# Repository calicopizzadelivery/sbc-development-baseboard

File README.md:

# sbc-development-baseboard

One board carrying the hardware you need to develop on and remotely manage an
attached single-board computer: a microcontroller that is a USB device to the
target and a console to you, four individually switched USB-A ports, an FTDI
header straight to the workstation, two isolated
SPDT relays on screw terminals, a level-shifted serial console, and a switched
supply for the target itself.

It replaces a bench that currently takes an FRDM-K64F, a QT Py, an 8-channel
relay board, a two-tier USB hub cascade and a CP2102N dongle, wired together by
hand and documented in a port map that has to be re-surveyed whenever anything
is replugged.

## What it does

| Function | How |
|---|---|
| Type at the target | USB HID keyboard + mouse from the K64's device port |
| Cut power to any USB device | Four USB-A ports on two stacked receptacles, each with its own current-limited switch |
| Hard power-cycle the target | Switched +5V_TGT rail up to 3 A behind an eFuse, or any PSU up to 30 V / 5 A through an isolated relay |
| Toggle target I/O — FORCE_RECOVERY and friends | Two SPDT relays, dry contacts, Phoenix terminals |
| Read the target's serial console | MCU-owned UART, auto level translation 1.2–3.6 V |
| Read it from the workstation directly | FT231X on an internal hub port, standard 6-pin FTDI header, 3.3 V |
| Do all of it from somewhere else | 10/100 Ethernet to the workstation |
| Do all of it with no network | USB CDC console over the onboard DAPLink |

Every one of those is addressable from the same ASCII protocol the relay
controller and the HID injector already speak — one line in, one line out,
starting `OK` or `ERR`. See **[docs/protocol.md](docs/protocol.md)**.

## The shape of it

```
workstation ──USB-C──> hub ──> 4x USB-A (switched)     ──> whatever you hang on the bench
                           ──> FT231X, FTDI header     ──> target's console, direct
            ──RJ45───> K64 ──> USB-C device port       ──> target's USB host port
                           ──> UART + VREF             ──> target's console
                           ──> 2x SPDT dry contacts    ──> target's recovery/reset pins
                           ──> switched +5V, 3 A       ──> target's supply
 target PSU ──Phoenix──> isolated relay, NO, 5 A       ──> target's supply, any voltage
 5 V adapter ──barrel──> +5V, one rail, 4 A, 20 W      ──> everything but the passthrough
```

140 × 100 mm, four M3 corner holes. Your connectors leave the left edge, the
target's the right; an LED on every rail, every switched output and every relay
coil, and none on the passthrough, whose voltage is whatever you plugged in.

One USB-C for the workstation and a barrel jack for power (2026-10-10; two
USB-C inlets, a PD charger beside the workstation port, until then). A
workstation port that carries data offers 15 W at best, and four switched ports
plus a target rail need more than that, so power has its own connector: a
5 V 4 A adapter on a 2.5 mm barrel jack, 20 W, which firmware budgets across
the ports and the target rail. A USB-C PD sink feeding two 5 V bucks did that
job first, and went because of what it cost the board rather than the bench:
339 parts became 270, and the one rail layer no longer carries a 3 A inlet
beside two 6 A rails, which is where the router stalled at 98 open connections
on six layers. Keeping power off the workstation link also means the board stays
alive when that link is down, so the MCU can power-cycle the entire USB tree
including its own path back to you.

## Where the design came from

Most of the non-obvious decisions here are bench scars from the Jetson work, not
preferences. They are written up in full in
**[docs/hardware-spec.md](docs/hardware-spec.md)**; the short version:

- **Nothing the MCU depends on sits downstream of a switch it controls.** The
  DAPLink, the Ethernet PHY and the MCU itself are all upstream. `OFF ALL` can
  never take out the console.
- **Rails boot to the state that does no harm.** USB ports and the target rail
  come up powered; relays come up de-energized. Resistors set this while the MCU
  is still in reset, so a reset never drops a load or asserts recovery.
- **The device port cannot back-feed the target.** Its VBUS is sense-only
  through a blocking element. This is the fix for the failure where cutting the
  target's power left it half-alive for 90 seconds because a self-powered
  FRDM-K64F was pushing 5 V up its own device port.
- **The relays are signal relays with gold-clad contacts.** Switching a 1.8 V
  logic pin is a dry circuit; silver power-relay contacts grow an oxide film
  that such a signal cannot break down.
- **The MCU owns the target's console.** No USB-UART bridge to wedge and look
  exactly like a target that is not booting.
- **The target's PSU passes through on its own nets.** A 19 V / 3 A return
  current has no business on the board's ground plane or its USB shields. It
  crosses one relay contact — normally open — so nothing powers until the
  baseboard says so, and a dead baseboard leaves the target off.

## Status

Specification, a generated schematic (KiCad 10, a root sheet and eight sub-sheets, ERC clean) and
a generated, placed six-layer board, both in
[`hardware/kicad/sbc-baseboard/`](hardware/kicad/sbc-baseboard/) with a
[PDF](hardware/kicad/sbc-baseboard/sbc-baseboard.pdf) of the schematic for
review. The board is placed and bulk-routed by the house standard's engine
(see [hardware/kicad/README.md](hardware/kicad/README.md)) and is being
routed again for the barrel-jack inlet (2026-10-10; the board routed before
it, with the PD inlet and the two bucks, stopped at 98 open connections on
six layers and 116 on four); the hand pass that finishes the routing is open.
No firmware.

Next: the routing and the hand pass on the board, then firmware.

## Layout

```
docs/hardware-spec.md   block diagram, part selection, power and pin budgets,
                        safe states, and the open questions
docs/protocol.md        the console protocol, across both transports
docs/block-diagram.*    the diagram above, SVG source and rendered PNG
scripts/block-diagram.py regenerates both; run it with every configuration change
hardware/kicad/         the KiCad project (sbc-baseboard/) and the generator that
                        produced its first pass (gen/) — see hardware/kicad/README.md
hardware/datasheets/    the parts that matter
```

## Related

- [`frdm-k64f-hid`](../frdm-k64f-hid) — the HID injector firmware this board inherits
- [`qtpy-relay-controller`](../qtpy-relay-controller) — the relay protocol and its safe-state rules
- [`nvidia-jetson-tv`](../nvidia-jetson-tv) — the target that motivated all of it

## Licence

Apache-2.0. See [LICENSE](LICENSE).

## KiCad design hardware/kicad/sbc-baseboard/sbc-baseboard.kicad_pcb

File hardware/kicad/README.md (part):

# KiCad project

`sbc-baseboard/` is the KiCad 10 project: a root sheet and eight sub-sheets,
a project symbol library for the parts the standard libraries lack, an ERC
report, a PDF of every sheet and a BOM.

```
sbc-baseboard/
  sbc-baseboard.kicad_pro   project
  sbc-baseboard.kicad_sch   root: sheet index, mounting holes, the verify-before-fab list
  power.kicad_sch           barrel-jack inlet J2, its TVS and reverse-polarity FET, +5V bulk, the +3V3 buck
  mcu.kicad_sch             K64, USB device port J3, SWD J16, heartbeat
  ethernet.kicad_sch        KSZ8081RNA, magjack
  hub.kicad_sch             USB2517, upstream J1, four switched USB-A, FT231X switch
  ftdi.kicad_sch            FT231X, J9 header, jumpers
  daplink.kicad_sch         MK20DX128 DAPLink
  target.kicad_sch          console, GPIO/I2C breakout, +5V_TGT eFuse
  relays.kicad_sch          two signal relays, PSU passthrough relay and its opto monitor
  libs/                     the house symbol libraries (ecad-libraries), a git submodule pinned to a tag
  sym-lib-table             names them calico-ic and calico-electromechanical, as ${KIPRJMOD}/../libs/...
                            and the stacked USB-A as two units (one per port)
  sbc-baseboard.pdf         all nine sheets
  erc.txt, bom.csv
```

Reference designators are numbered by sheet: R1xx/C1xx power (the inlet
and the +3V3 buck), 2xx MCU, 3xx Ethernet, 4xx hub, 5xx FTDI, 6xx DAPLink,
7xx target I/O (the +5V_TGT eFuse among them), 8xx relays and passthrough.

## How it was made, and the handoff

The schematic was **generated**, by `gen/build.py`. That generator pulls
symbols from KiCad's own libraries (so the embedded copies match what KiCad
ships), builds the missing symbols from datasheet pin tables, lays each sheet
out around its main component (`gen/fanout.py`: lanes leave the IC's pins at
pin pitch, and connectors, series parts, pull-ups and power symbols are drawn
at the ends of the lanes — the style in
[ecad-standards](https://github.com/calicopizzadelivery/ecad-standards)), and
writes the `.kicad_sch` files directly. It then runs `kicad-cli sch erc` and
exports the PDF and BOM. Pin-position maths and power-symbol net naming were
calibrated against `kicad-cli`'s netlist export before any real sheet was
built.

Five checks guard every build and all pass at zero: `kicad-cli sch erc
--severity-all`; `gen/check_geom.py`, which finds wire ends and pin ends that
land on a foreign wire with no junction (the shorts a netlist shows only as a
merged net) and any two wires drawn over each other;
`gen/netcheck.py`, which traces wire-level connectivity in each sheet and
reports any net carrying two rails; and `gen/check_layout.py`, which reports
text over outlines, wires or other text, wires through a part body, and power
symbols pointing the wrong way (GND always hangs down, rails always stand up),
anything on the sheet frame or the title block, pin numbers treated as text
like any other, and pin names inside a symbol that print over each other
(`gen/check_pins.py`, run on library symbols too; its `--gaps` option lists the
closest name pairs). Text widths come from a per-glyph table fitted to the text
extents KiCad writes into its own PDF export. The fifth is reproducibility:
build, `git add` the outputs, build again, and `git status` must be empty. The netlist was also diffed against the
first label-style pass with passive renumbering factored out, so the re-layout
changed drawing, not connectivity (the JP501 default and the J1 VBUS divider
tap, which became a local label, are the two intended exceptions).

**Nothing is drawn over anything else.** Routes into a stacked connector
from one side take staggered columns and rows (the route bound for the
farthest pin gets the outermost column and the nearest row), a tag before a
route ends where the route's target lies, several routes into one pin share
one stub, and a second tap on a wire lands beside the first, never on it.
The geometry check is at zero on every sheet: no wire end on a foreign wire
without a junction, no two wires sharing a stretch.

**The FTDI header is an Adafruit FTDI Friend.** J9 is GND, CTS, VCC, TX, RX,
RTS in that order; VCC is 5 V by default (JP502, bridged A–C) or 3.3 V from
the FT231X's regulator (B–C); pin 6 is RTS by default (JP501, bridged A–C)
or DTR. Logic is 3.3 V. The first pass left J9's VCC pin on an open jumper
only, so it floated by default; the bridged jumpers fix that.

**The DAPLink K20 follows the FRDM-K64F OpenSDA circuit.** DAPLink's k20dx
port reads SWDIO on PTC7 and drives it on PTC6, so both are on the SWDIO
net; the FRDM's 33 Ω series resistors on the K20's USB pair are fitted. See
[reference-design-review.md](../../docs/reference-design-review.md).

**Differential pairs are named for the router.** Every USB 2.0 pair carries
net names `<base>_P` / `<base>_N`, the suffixes KiCad's PCB editor pairs up:
`J1_D`, `J3_D` and `PORT1_D`..`PORT4_D` on the receptacle side of each ESD
array, `HUB_UP` and `HUB_DN1`..`HUB_DN7` at the hub, `K64_USB` and
`FTDI_USB` at the chips (the ESD arrays' pass-through pins and the FT231X's
series resistors each split a pair into two nets, and both halves are named).
The project file carries a `USB` net class matched by pattern
(`*_USB_?`, `*_D_?`, `*HUB_UP_?`, `*HUB_DN?_?`); the patterns are globs over
the full hierarchical name, so a sheet-local net such as `/USB hub/PORT1_VBUS`
is matched only by a pattern that starts with `*` (the port VBUS nets sat in
`Default` until 2026-10-08 for want of that star, and the standard's engine
now stops on a class that no net resolves to). Its differential width and
gap are 0.33 / 0.20 mm, 90 Ω over the ground plane beside each outer layer on
the six-layer stackup (the fab's calculator rules when the stackup is
confirmed); the `ETH` class 0.29 / 0.25 mm for 100 Ω. Route each pair as a pair, no stubs,
over an unbroken reference plane. The power classes are matched the same
way: `PWR_4A` (2.5 mm tracks or pours, 1.0 mm / 0.5 mm vias, three rail vias
per pad) for `+5V` and `*+5V_TGT`, the one inlet rail and the eFuse's
switched output (2026-10-10; until then `PWR_6A` carried the two bucks'
6 A outputs and the PD inlet's `VBUS_IN` ran at 3 A); `USB_VBUS_3A` (2 mm,
1.0 mm vias) for `*PORT?_VBUS` and `*FTDI_VBUS` only; `PWR_1A` (0.6 mm) for
`+3V3`; `PSU_3A` and `PSU_ISO` for the passthrough and its sense lines;
`Default` at 0.2 mm.

**Builds are reproducible.** Every UUID in the generated files is derived,
not drawn: a UUID5 in a namespace made from the project name, keyed by what
the element is (a symbol by its reference and unit, a pin by its symbol, a
wire by its sheet and ends, a label by its sheet, net and position, a sheet by
its file name; identical keys get a counter in draw order). The ERC report
header and the PDF's creation date are pinned to the title-block date. So two
builds of one design give byte-identical files, a commit touches only the
sheets whose design changed, and once layout starts a regenerated sheet keeps
its footprints linked, since the board links footprints to symbols by UUID
path. The costs are the ones KiCad itself has: renaming a reference is a new
symbol, moving a wire or label is a new UUID (nothing outside the sheet refers
to those), and the power symbols, numbered in draw order per sheet, renumber
when one is inserted before them. Keep it that way: never write a random UUID
into the output, and never let an export's timestamp into a tracked file.

**The generator is bring-up tooling, not the source of truth.** The moment
anyone edits the schematic in KiCad, the KiCad files are the design and
`gen/` is history: re-running `build.py` would overwrite the edits. The honest
next step is layout.

```bash
cd gen && ./build.py        # regenerate everything (only while nothing has been hand-edited)
```

## Layout

The board file `sbc-baseboard.kicad_pcb` was generated once, by the
standard's placement engine (`standards/tools/placer.py`, the ecad-standards
repository as a submodule at `standards/`, on KiCad's `pcbnew` Python module)
called from `gen/pcb.py`, from the schematic's netlist, the project file and
the directives in `gen/layout.py`, which are
[docs/layout-directives.md](../../docs/layout-directives.md) as data. It
carries the 140 × 100 mm outline with 2 mm corners, the four M3 holes on GND
7 mm from the corners with their corner keep-outs, Advanced Circuits' 6-layer
stackup, the 270 footprints with their nets (339 until 2026-10-10, when the
USB-C PD inlet, its STUSB4500 controller, bus buffer and programming header
and the two 5 V bucks went and a barrel jack came; 481 connections, 499
before), the L2 and L5 ground planes with the isolated PSU_GND islands, and
`sbc-baseboard.kicad_dru` with the passthrough's isolation rules.

The placement follows
[ecad-standards/layout.md](https://github.com/calicopizzadelivery/ecad-standards/blob/main/layout.md)
section 3: the edge connectors are locked at the directives' positions,
facing outward; the ICs are anchored by flow (the table in the directives:
power enters at J2 on the left edge, its reverse-polarity FET Q101 anchored
at (20, 30) behind the jack with the TVS, gate pull-down, bulk capacitors
and LED around it as the inlet island, the +3V3 buck U105 at (41, 41) as
the one regulator city, laid out from its datasheet figure, and the eFuse
U704 behind J14; the corner the two bucks occupied, x 10..70, y 3..36, is
largely empty since 2026-10-10);
the two parts that straddle the isolation barrier are fixed; every other
part is placed at the pin it serves, by the generator, in five passes (small
decoupling capacitors at their pins, the large parts on an IC's own pins,
bulk capacitors, the small parts on those pins, then parts hosted by other
passives), each on its host's nearest side with the pad on the host's net
facing it, packed outward in rings; since 2026-10-10 the owner's hand
placement outranks all of this (the directives' Placement section: the
saved board is harvested into `gen/hand_placement.py` by the standard's
`tools/handplace.py`, every part fixed where the owner put it, and the
generator reproduces it), so the engine's own placement is what a part
gets until the owner moves it; since 2026-10-15 the standard's `tools/live.py`
runs the lane check on the board open in the PCB editor over KiCad's IPC
API and selects the parts that stand in a lane, so a move is judged as it
is made (from this directory: `standards/tools/bootstrap.sh` once, "Enable
KiCad API" in KiCad's preferences, then `standards/.venv/bin/python
standards/tools/live.py check gen --select`). Small resistors, capacitors, diodes and
transistors that are not on a current-carrying, pair or switching-loop net go
to the bottom, tucked under their host's pin row, clear of through-hole pads
and exposed-pad via fields (the directives' Sides section); the rest stay on
top. The lanes the directives declare (the PSU passthrough: J18 to the relay
to J19) are laid first as footprint keep-outs on both sides and as 2 mm
tracks, so nothing is placed in the way of the 3 A path. ESD parts go down
before anything else, on top, in the first ring at their connector's signal
pins; the USB arrays are flow-through, turned with their receptacle-side
pins toward the receptacle, and both nets of each pair are in the `USB`
class (the schematic build refuses a `_P`/`_N` pair outside it). `placement.txt`
records every part's host, side and ring; the generator prints the parts it
could not keep within 8 mm of their pin. The silkscreen pass places each reference designator where it
overlaps nothing (1.0 mm, then 0.8 mm text) and omits it otherwise, per the
standard's section 6; ICs and connectors are never omitted, their designator
steps out to the nearest pocket instead, and the generator lists those too.
The fabrication layer keeps every designator.

The pairs are laid by the engine as pair lanes (both members at the class's
differential geometry, escapes, the USB-C bridges, two layer changes where
a pair must pass under the port pairs, lengths matched by a bump), the ESD
arrays and series parts anchored for it; the PSU passthrough is laid as
single-net lanes; the one rail, +5V, is a chain of rectangles on L4
referenced to the L5 ground plane, from the jack (x 3..42, y 22..40)
through the 3V3 buck's input, down beside the relay region, along the port
switches, across above the passthrough region to the FTDI switch, the
relays and the eFuse behind J14, which the standard's rails gate holds to
one piece (2026-10-10; until then VBUS_IN, +5V_PORTS and +5V_TGT were
three rails on that layer, the two 6 A ones and the 3 A inlet competing
for it); +5V_TGT leaves the eFuse to J14 as a track in the same class;
+3V3 is routed, in its 0.6 mm `PWR_1A` class, since on six layers a plane
for it would cost the third routing layer. What is left is routed by
FreeRouting through the standard's `tools/autoroute.py` with all of that
locked (`gen/pcb.py --route`; the directives' `FREEROUTING` setting names
the binary), and the hand pass finishes from there. KiCad Routing Tools
was tried on the same board as a second opinion (2026-10-07): two hours in
it had 25 connections left and 1 646 DRC errors, having routed below the
fab's track and via floors and through the keep-outs; FreeRouting honours
the Specctra rules and the fixed lanes, so it stays the bulk router.

`gen/pcb.py` also runs `kicad-cli pcb drc --severity-all --refill-zones`
(the planes are filled for the check and not saved, so a plane that fails to
fill or strays into a keep-out shows; the unconnected count is the ratsnest's
and does not credit the planes); its report is `drc.txt`.

The board as last routed (2026-10-09, six layers, with the PD inlet and the
two bucks still on it; the barrel-jack board of 2026-10-10 started from a
copper reset and is being placed by hand before it is routed again, so
until that routing is committed these are the previous board's figures) is the engine's
placement on the 140 × 100 mm outline, bulk-routed by FreeRouting on L1,
L3 and L6 over the locked lanes, rail vias and planes (`gen/pcb.py --route
--copper`, 24 passes, 5 h 12 min on one thread of which 55 min were its
fanout stage, 122 open connections by its own count after its optimiser)
and given the standard's copper pass: 3 050 track segments, 42 % of the
track length on the top, 37 % on L3 and 21 % on the bottom (of the
router's own, 47 % on L3); 939 vias, of which 237 are the rail vias beside
the pads on the plane nets (156 on ground, 39 on +5V_PORTS, 26 on VBUS_IN,
14 on +5V_TGT, 2 on the passthrough's ground; 14 pads fewer than their
class's count and 115 none at all, both listed in `placement.txt`), 24 the
lanes' own layer changes, 332 ground stitching on the 5 mm grid (2.3
stitching vias per cm² outside the isolated region, 3.5 ground vias per
cm² with the rail vias) and 346 the router's; ground floods over 54 % of
the top and 67 % of the bottom, notched around the passthrough block,
which floods its own `PSU_GND`, all saved filled; the ground planes on L2
and L5 over 76 % each. The three L4 rails are each one piece; +3V3 is
routed at 0.6 mm, 243 segments and 496 mm. The 282 lane tracks are locked
and intact: nine pairs matched to 0.00 mm (six by bumps, three by
symmetric legs), the two Ethernet pairs 2.5 mm apart over their 7.4 to
10.9 mm from jack to PHY, where no bump fits. The router laid the wide
classes at the 2 mm cap apart from the pad-entry necks; five segments run
on at a pad's width more than a millimetre beyond the pad (three on +3V3,
one each on +5V_PORTS and FTDI_VBUS) and are listed for the hand pass to
widen. 98 of the 499 connections
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
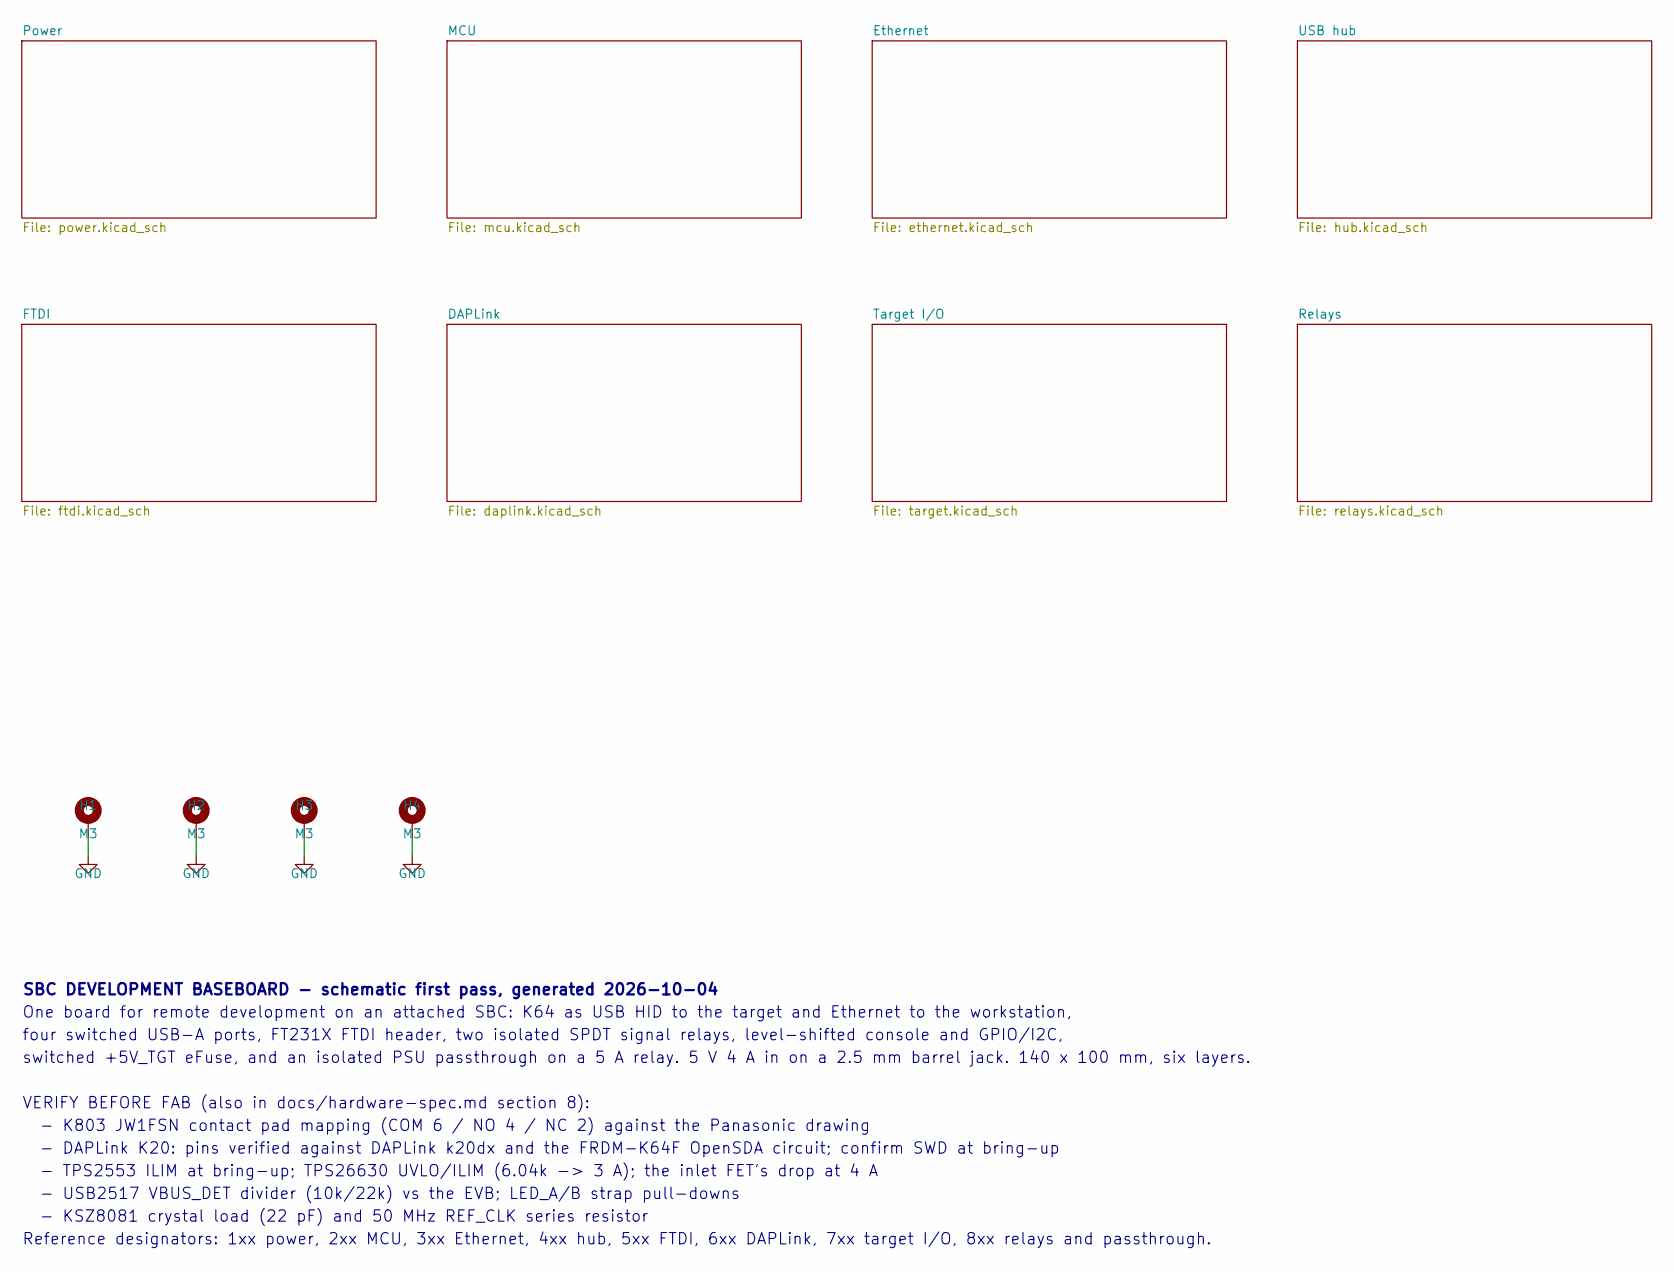
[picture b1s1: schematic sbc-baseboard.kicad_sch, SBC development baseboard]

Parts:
H1, H2, H3, H4: M3; MountingHole_3.2mm_M3_Pad

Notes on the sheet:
SBC DEVELOPMENT BASEBOARD - schematic first pass, generated 2026-10-04
One board for remote development on an attached SBC: K64 as USB HID to the target and Ethernet to the workstation,
four switched USB-A ports, FT231X FTDI header, two isolated SPDT signal relays, level-shifted console and GPIO/I2C,
switched +5V_TGT eFuse, and an isolated PSU passthrough on a 5 A relay. 5 V 4 A in on a 2.5 mm barrel jack. 140 x 100 mm, six layers.
VERIFY BEFORE FAB (also in docs/hardware-spec.md section 8):
- K803 JW1FSN contact pad mapping (COM 6 / NO 4 / NC 2) against the Panasonic drawing
- DAPLink K20: pins verified against DAPLink k20dx and the FRDM-K64F OpenSDA circuit; confirm SWD at bring-up
- TPS2553 ILIM at bring-up; TPS26630 UVLO/ILIM (6.04k -> 3 A); the inlet FET's drop at 4 A
- USB2517 VBUS_DET divider (10k/22k) vs the EVB; LED_A/B strap pull-downs
- KSZ8081 crystal load (22 pF) and 50 MHz REF_CLK series resistor
Reference designators: 1xx power, 2xx MCU, 3xx Ethernet, 4xx hub, 5xx FTDI, 6xx DAPLink, 7xx target I/O, 8xx relays and passthrough.

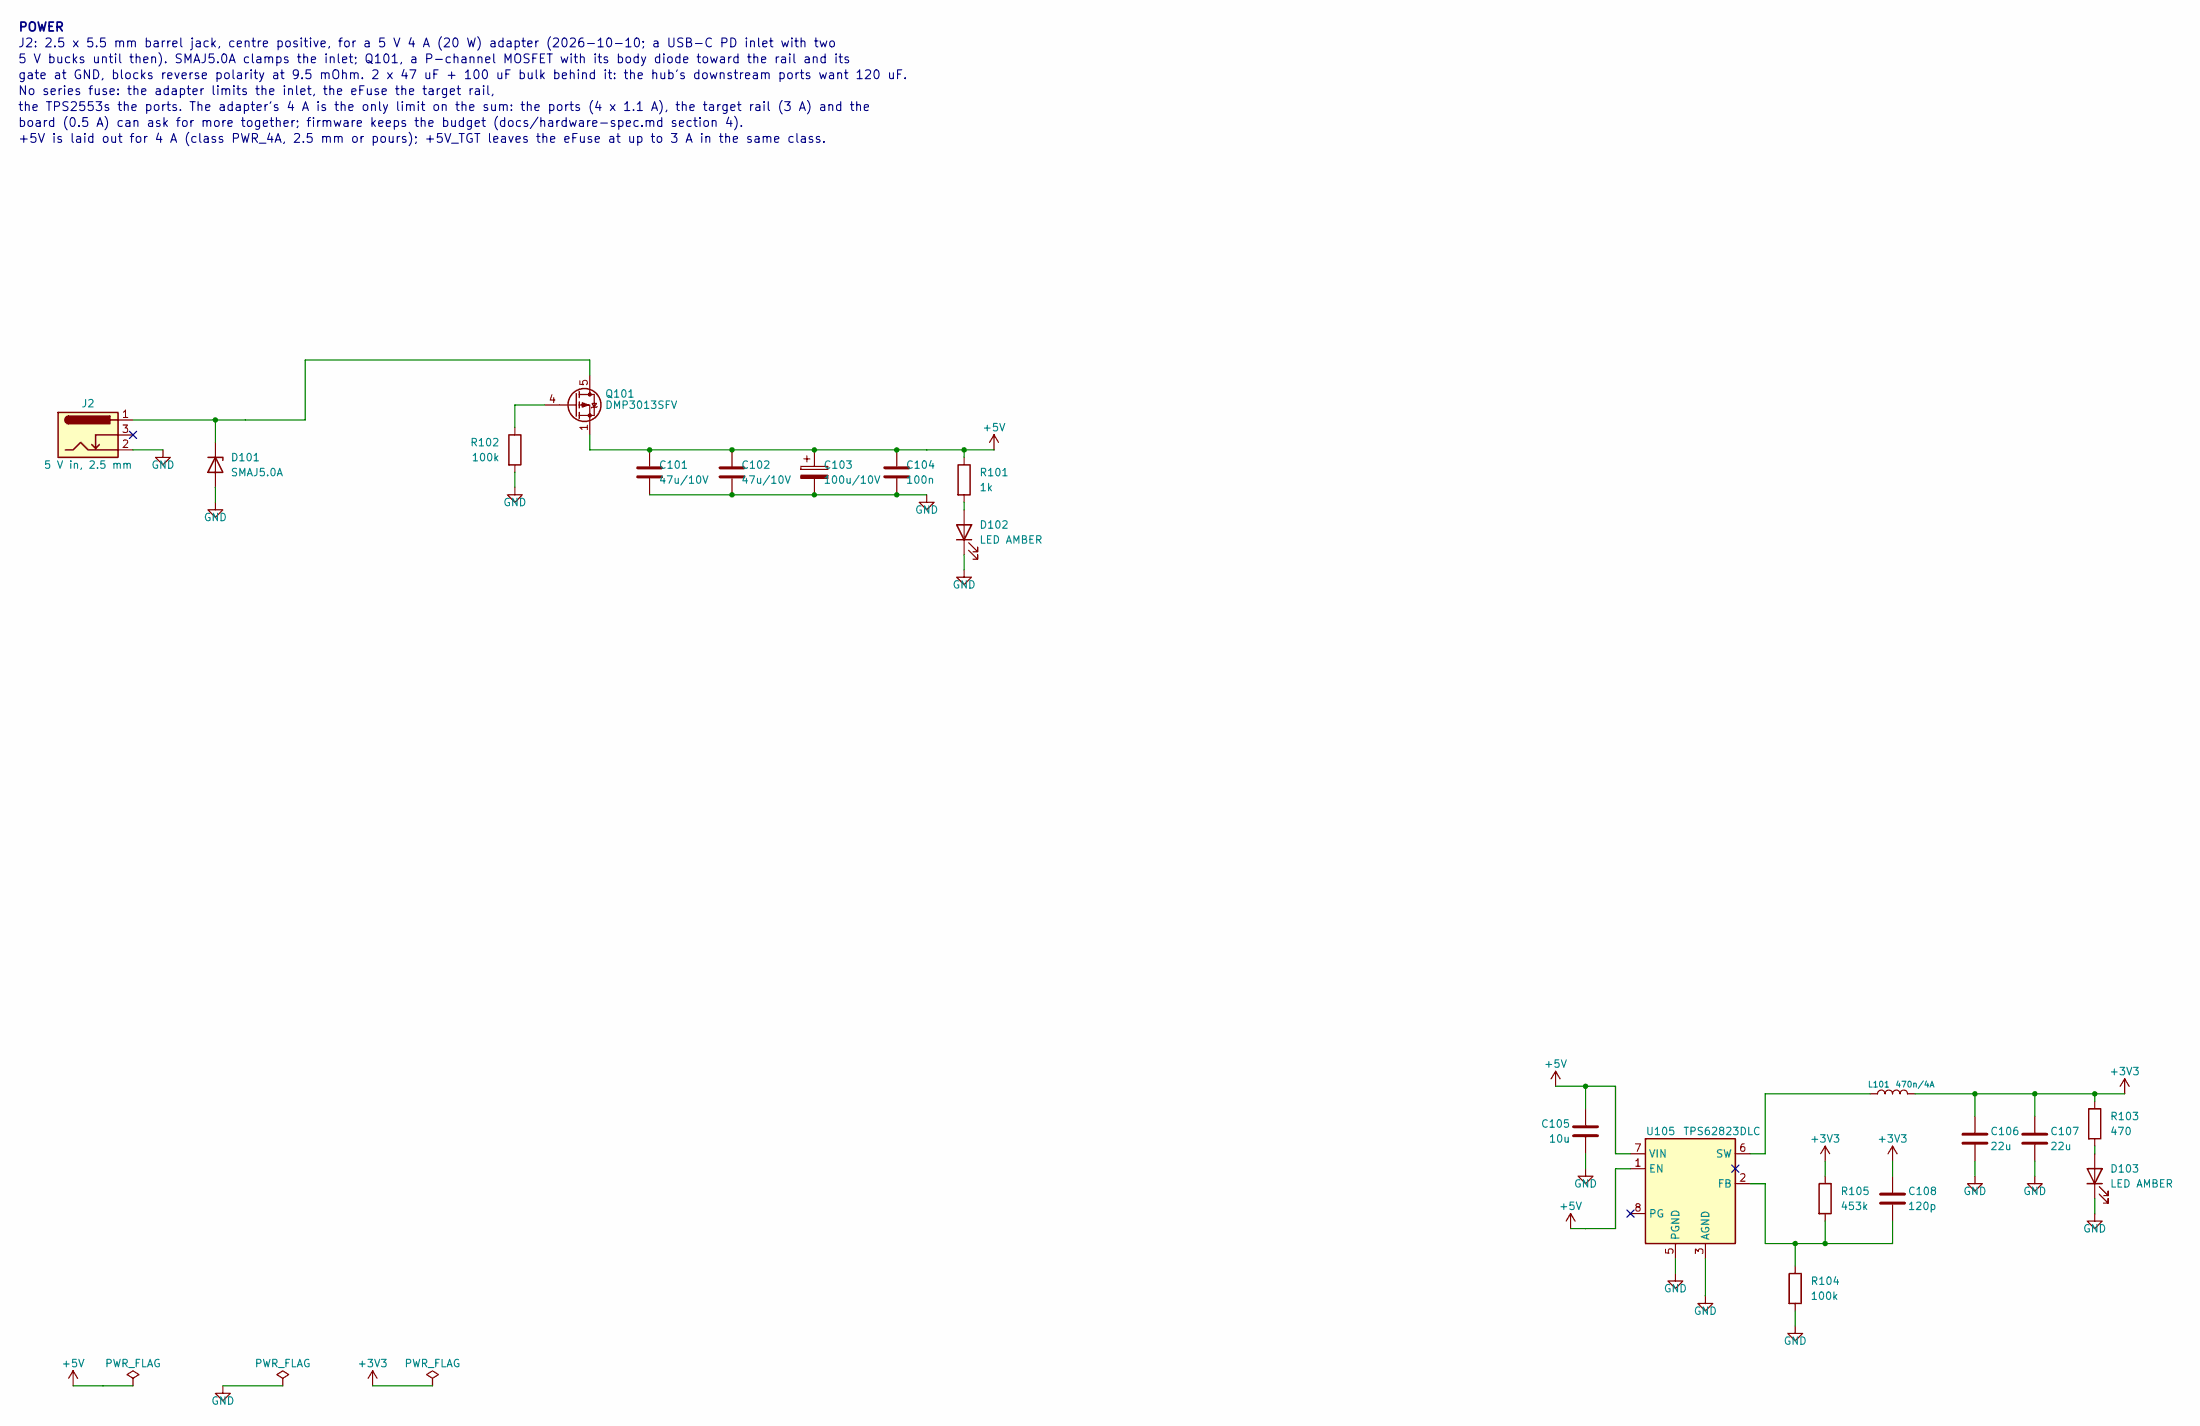
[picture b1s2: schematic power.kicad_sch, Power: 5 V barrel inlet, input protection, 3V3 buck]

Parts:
C101, C102: 47u/10V; C_1210_3225Metric
C103: 100u/10V; CP_Elec_8x10.5
C104: 100n; C_0603_1608Metric
C105: 10u; C_0805_2012Metric
C106, C107: 22u; C_0805_2012Metric
C108: 120p; C_0603_1608Metric
D101: SMAJ5.0A; D_SMA
D102, D103: LED AMBER; LED_0603_1608Metric
J2: 5 V in, 2.5 mm; BarrelJack_Kycon_KLDX-0202-xC_Horizontal
L101: 470n/4A; L_1210_3225Metric
Q101: DMP3013SFV; Diodes_PowerDI3333-8
R101: 1k; R_0603_1608Metric
R102, R104: 100k; R_0603_1608Metric
R103: 470; R_0603_1608Metric
R105: 453k; R_0603_1608Metric
U105: TPS62823DLC; Texas_VSON-HR-8_1.5x2mm_P0.5mm

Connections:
unnamed: D101.1 (K), J2.1, Q101.5 (D)
unnamed: D102.2 (A), R101.2
unnamed: D103.2 (A), R103.2
unnamed: Q101.4 (G), R102.1
unnamed: C108.2, R104.1, R105.2, U105.2 (FB)
unnamed: L101.1, U105.6 (SW)

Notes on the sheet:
POWER
J2: 2.5 x 5.5 mm barrel jack, centre positive, for a 5 V 4 A (20 W) adapter (2026-10-10; a USB-C PD inlet with two
5 V bucks until then). SMAJ5.0A clamps the inlet; Q101, a P-channel MOSFET with its body diode toward the rail and its
gate at GND, blocks reverse polarity at 9.5 mOhm. 2 x 47 uF + 100 uF bulk behind it: the hub's downstream ports want 120 uF.
No series fuse: the adapter limits the inlet, the eFuse the target rail,
the TPS2553s the ports. The adapter's 4 A is the only limit on the sum: the ports (4 x 1.1 A), the target rail (3 A) and the
board (0.5 A) can ask for more together; firmware keeps the budget (docs/hardware-spec.md section 4).
+5V is laid out for 4 A (class PWR_4A, 2.5 mm or pours); +5V_TGT leaves the eFuse at up to 3 A in the same class.

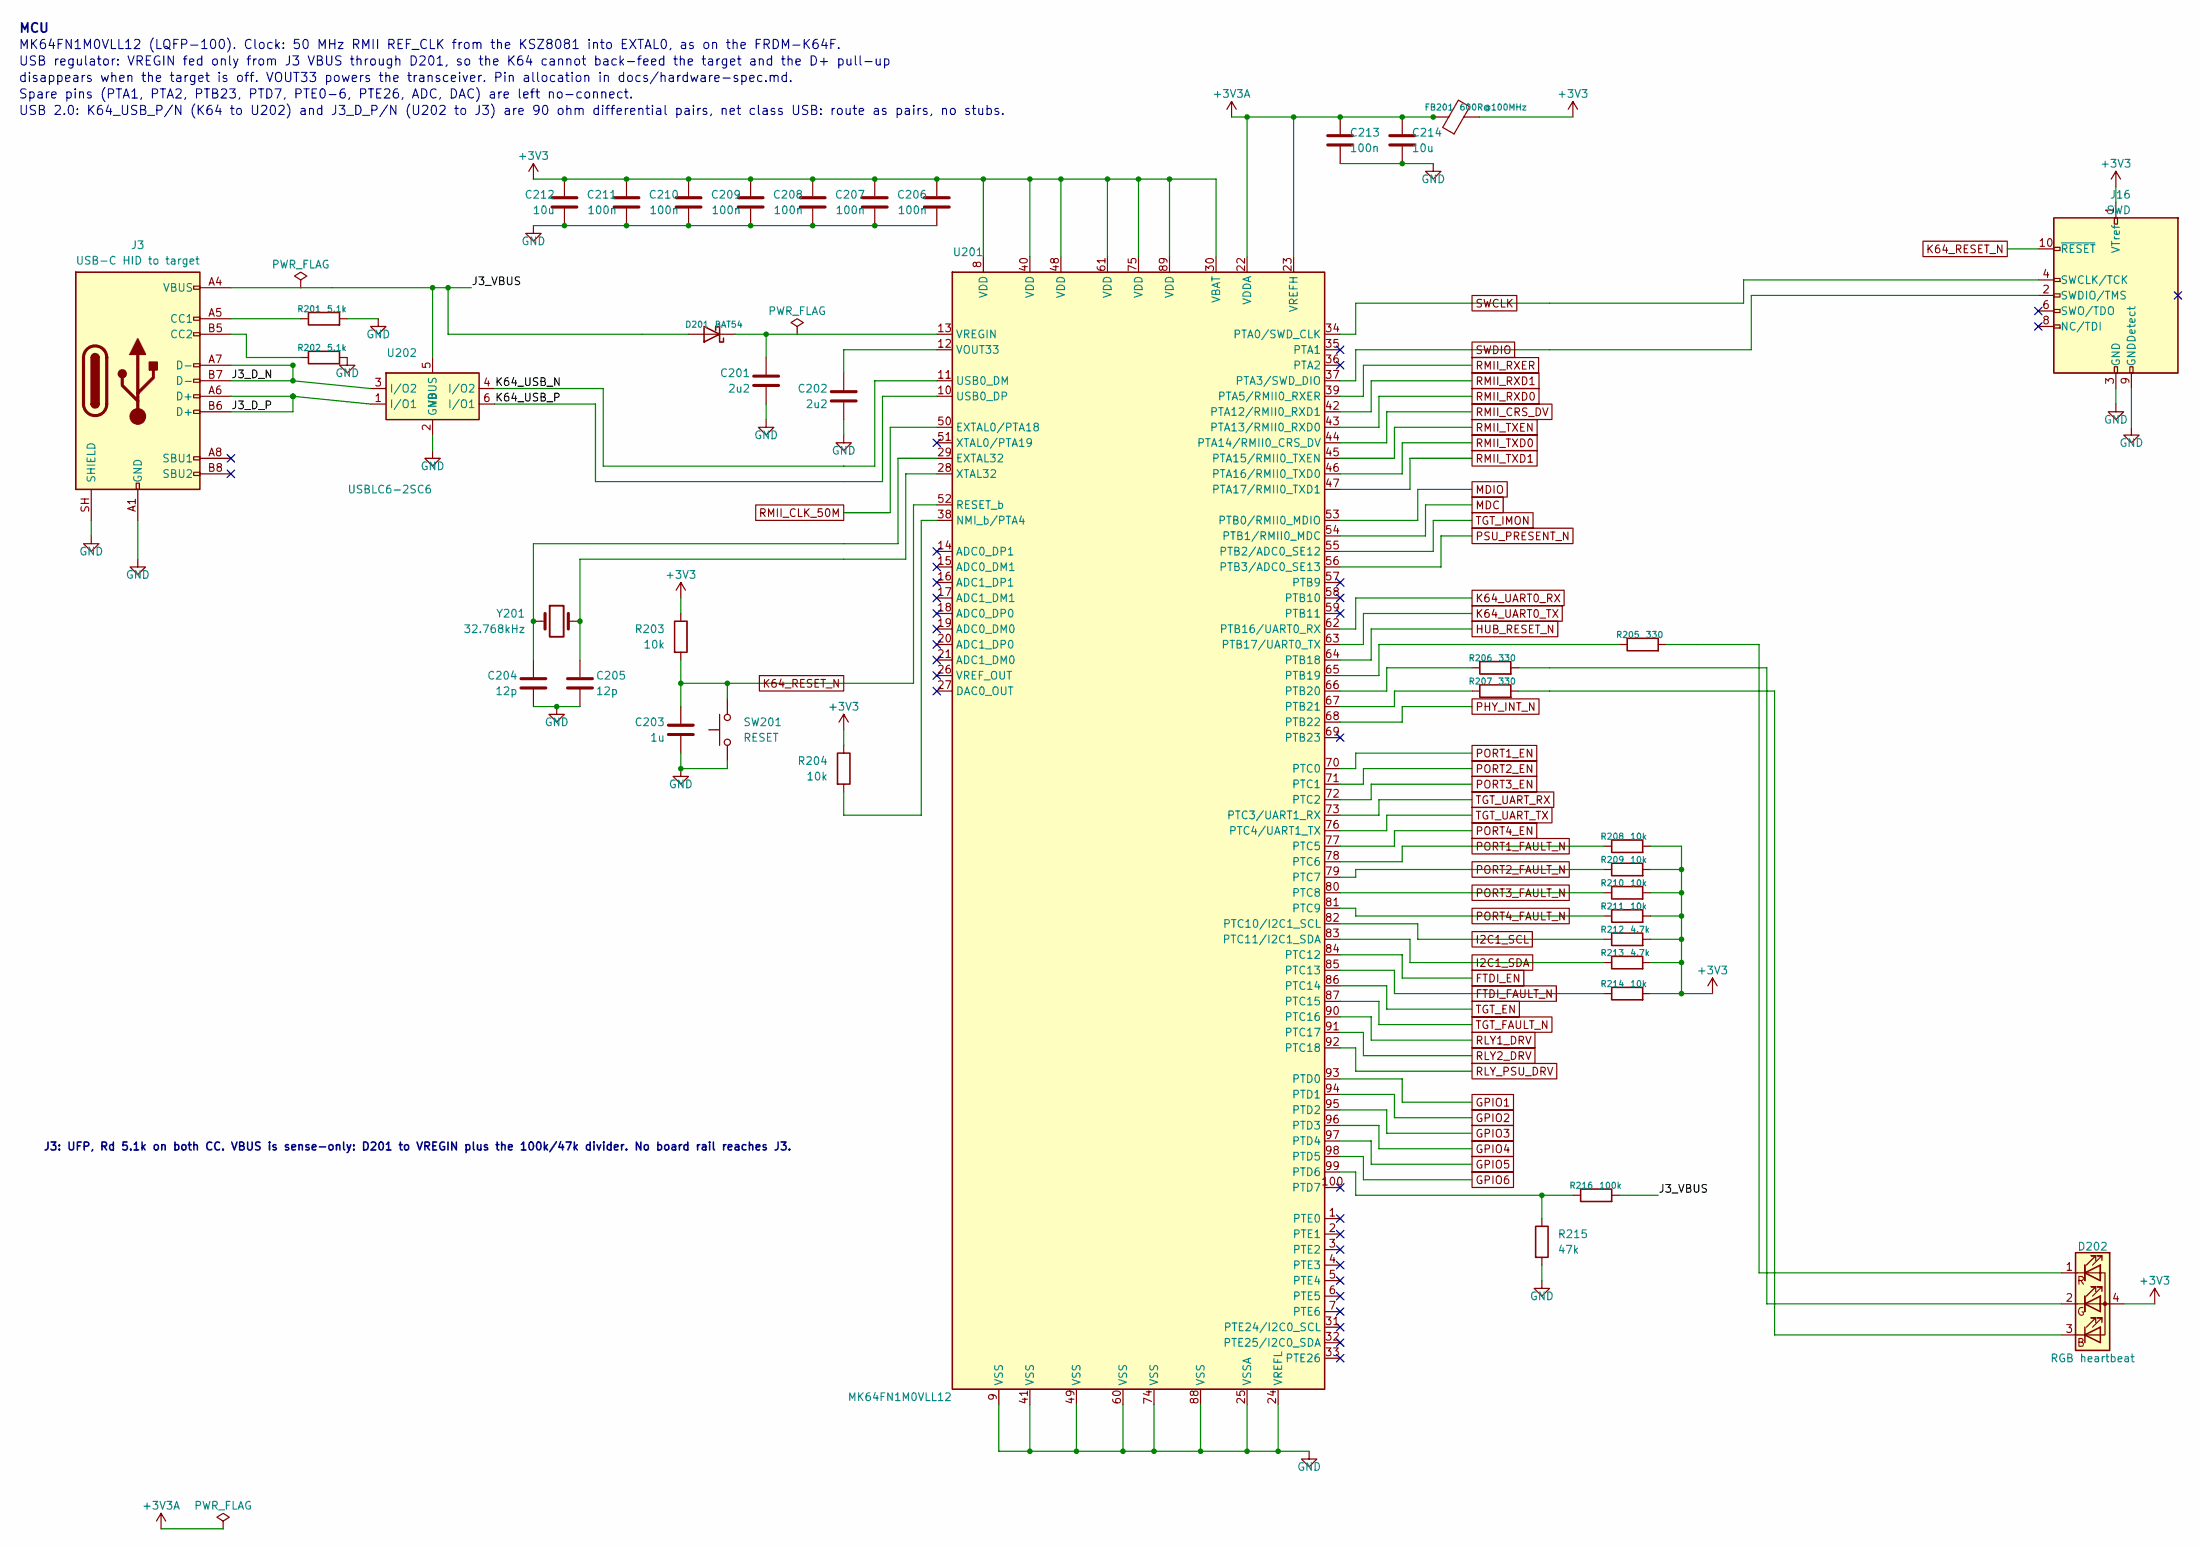
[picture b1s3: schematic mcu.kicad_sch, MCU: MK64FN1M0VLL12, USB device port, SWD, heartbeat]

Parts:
C201, C202: 2u2; C_0603_1608Metric
C203: 1u; C_0603_1608Metric
C204, C205: 12p; C_0603_1608Metric
C206, C207, C208, C209, C210, C211, C213: 100n; C_0603_1608Metric
C212, C214: 10u; C_0805_2012Metric
D201: BAT54; D_SOD-123
D202: RGB heartbeat; LED_RGB_1210
FB201: 600R@100MHz; L_0603_1608Metric
J3: USB-C HID to target; USB_C_Receptacle_GCT_USB4105-xx-A_16P_TopMnt_Horizontal_Peg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
J16: SWD; PinHeader_2x05_P1.27mm_Vertical
R201, R202: 5.1k; R_0603_1608Metric
R203, R204, R208, R209, R210, R211, R214: 10k; R_0603_1608Metric
R205, R206, R207: 330; R_0603_1608Metric
R212, R213: 4.7k; R_0603_1608Metric
R215: 47k; R_0603_1608Metric
R216: 100k; R_0603_1608Metric
SW201: RESET; SW_SPST_PTS645Sx43SMTR92
U201: MK64FN1M0VLL12; LQFP-100_14x14mm_P0.5mm
U202: USBLC6-2SC6; SOT-23-6
Y201: 32.768kHz; Crystal_SMD_3215-2Pin_3.2x1.5mm

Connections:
/MCU/J3_D_N: J3.A7 (D-), J3.B7 (D-), U202.3 (I/O2)
/MCU/J3_D_P: J3.A6 (D+), J3.B6 (D+), U202.1 (I/O1)
/MCU/K64_USB_N: U201.11 (USB0_DM), U202.4 (I/O2)
/MCU/K64_USB_P: U201.10 (USB0_DP), U202.6 (I/O1)
FTDI_EN: U201.84 (PTC12); also elsewhere on the board
FTDI_FAULT_N: R214.1, U201.85 (PTC13); also elsewhere on the board
GPIO1: U201.93 (PTD0); also elsewhere on the board
GPIO2: U201.94 (PTD1); also elsewhere on the board
GPIO3: U201.95 (PTD2); also elsewhere on the board
GPIO4: U201.96 (PTD3); also elsewhere on the board
GPIO5: U201.97 (PTD4); also elsewhere on the board
GPIO6: U201.98 (PTD5); also elsewhere on the board
HUB_RESET_N: U201.64 (PTB18); also elsewhere on the board
I2C1_SCL: R212.1, U201.82 (PTC10/I2C1_SCL); also elsewhere on the board
I2C1_SDA: R213.1, U201.83 (PTC11/I2C1_SDA); also elsewhere on the board
K64_RESET_N: C203.1, J16.10 (~RESET), R203.2, SW201.2, U201.52 (RESET_b); also elsewhere on the board
K64_UART0_RX: U201.62 (PTB16/UART0_RX); also elsewhere on the board
K64_UART0_TX: U201.63 (PTB17/UART0_TX); also elsewhere on the board
MDC: U201.54 (PTB1/RMII0_MDC); also elsewhere on the board
MDIO: U201.53 (PTB0/RMII0_MDIO); also elsewhere on the board
unnamed: D202.3 (BK), R207.2
unnamed: D202.2 (GK), R206.2
unnamed: D202.1 (RK), R205.2
unnamed: J3.A5 (CC1), R201.1
unnamed: J3.B5 (CC2), R202.1
unnamed: C204.1, U201.29 (EXTAL32), Y201.1
unnamed: R204.2, U201.38 (NMI_b/PTA4)
unnamed: R205.1, U201.65 (PTB19)
unnamed: R206.1, U201.66 (PTB20)
unnamed: R207.1, U201.67 (PTB21)
unnamed: R215.1, R216.1, U201.99 (PTD6)
unnamed: C202.1, U201.12 (VOUT33)
unnamed: C205.1, U201.28 (XTAL32), Y201.2
PHY_INT_N: U201.68 (PTB22); also elsewhere on the board
PORT1_EN: U201.70 (PTC0); also elsewhere on the board
PORT1_FAULT_N: R208.1, U201.78 (PTC6); also elsewhere on the board
PORT2_EN: U201.71 (PTC1); also elsewhere on the board
PORT2_FAULT_N: R209.1, U201.79 (PTC7); also elsewhere on the board
PORT3_EN: U201.72 (PTC2); also elsewhere on the board
PORT3_FAULT_N: R210.1, U201.80 (PTC8); also elsewhere on the board
PORT4_EN: U201.77 (PTC5); also elsewhere on the board
PORT4_FAULT_N: R211.1, U201.81 (PTC9); also elsewhere on the board
PSU_PRESENT_N: U201.56 (PTB3/ADC0_SE13); also elsewhere on the board
RLY1_DRV: U201.90 (PTC16); also elsewhere on the board
RLY2_DRV: U201.91 (PTC17); also elsewhere on the board
RLY_PSU_DRV: U201.92 (PTC18); also elsewhere on the board
RMII_CLK_50M: U201.50 (EXTAL0/PTA18); also elsewhere on the board
RMII_CRS_DV: U201.44 (PTA14/RMII0_CRS_DV); also elsewhere on the board
RMII_RXD0: U201.43 (PTA13/RMII0_RXD0); also elsewhere on the board
RMII_RXD1: U201.42 (PTA12/RMII0_RXD1); also elsewhere on the board
RMII_RXER: U201.39 (PTA5/RMII0_RXER); also elsewhere on the board
RMII_TXD0: U201.46 (PTA16/RMII0_TXD0); also elsewhere on the board
RMII_TXD1: U201.47 (PTA17/RMII0_TXD1); also elsewhere on the board
RMII_TXEN: U201.45 (PTA15/RMII0_TXEN); also elsewhere on the board
SWCLK: J16.4 (SWCLK/TCK), U201.34 (PTA0/SWD_CLK); also elsewhere on the board
SWDIO: J16.2 (SWDIO/TMS), U201.37 (PTA3/SWD_DIO); also elsewhere on the board
TGT_EN: U201.86 (PTC14); also elsewhere on the board
TGT_FAULT_N: U201.87 (PTC15); also elsewhere on the board
TGT_IMON: U201.55 (PTB2/ADC0_SE12); also elsewhere on the board
TGT_UART_RX: U201.73 (PTC3/UART1_RX); also elsewhere on the board
TGT_UART_TX: U201.76 (PTC4/UART1_TX); also elsewhere on the board

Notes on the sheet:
MCU
MK64FN1M0VLL12 (LQFP-100). Clock: 50 MHz RMII REF_CLK from the KSZ8081 into EXTAL0, as on the FRDM-K64F.
USB regulator: VREGIN fed only from J3 VBUS through D201, so the K64 cannot back-feed the target and the D+ pull-up
disappears when the target is off. VOUT33 powers the transceiver. Pin allocation in docs/hardware-spec.md.
Spare pins (PTA1, PTA2, PTB23, PTD7, PTE0-6, PTE26, ADC, DAC) are left no-connect.
USB 2.0: K64_USB_P/N (K64 to U202) and J3_D_P/N (U202 to J3) are 90 ohm differential pairs, net class USB: route as pairs, no stubs.
J3: UFP, Rd 5.1k on both CC. VBUS is sense-only: D201 to VREGIN plus the 100k/47k divider. No board rail reaches J3.

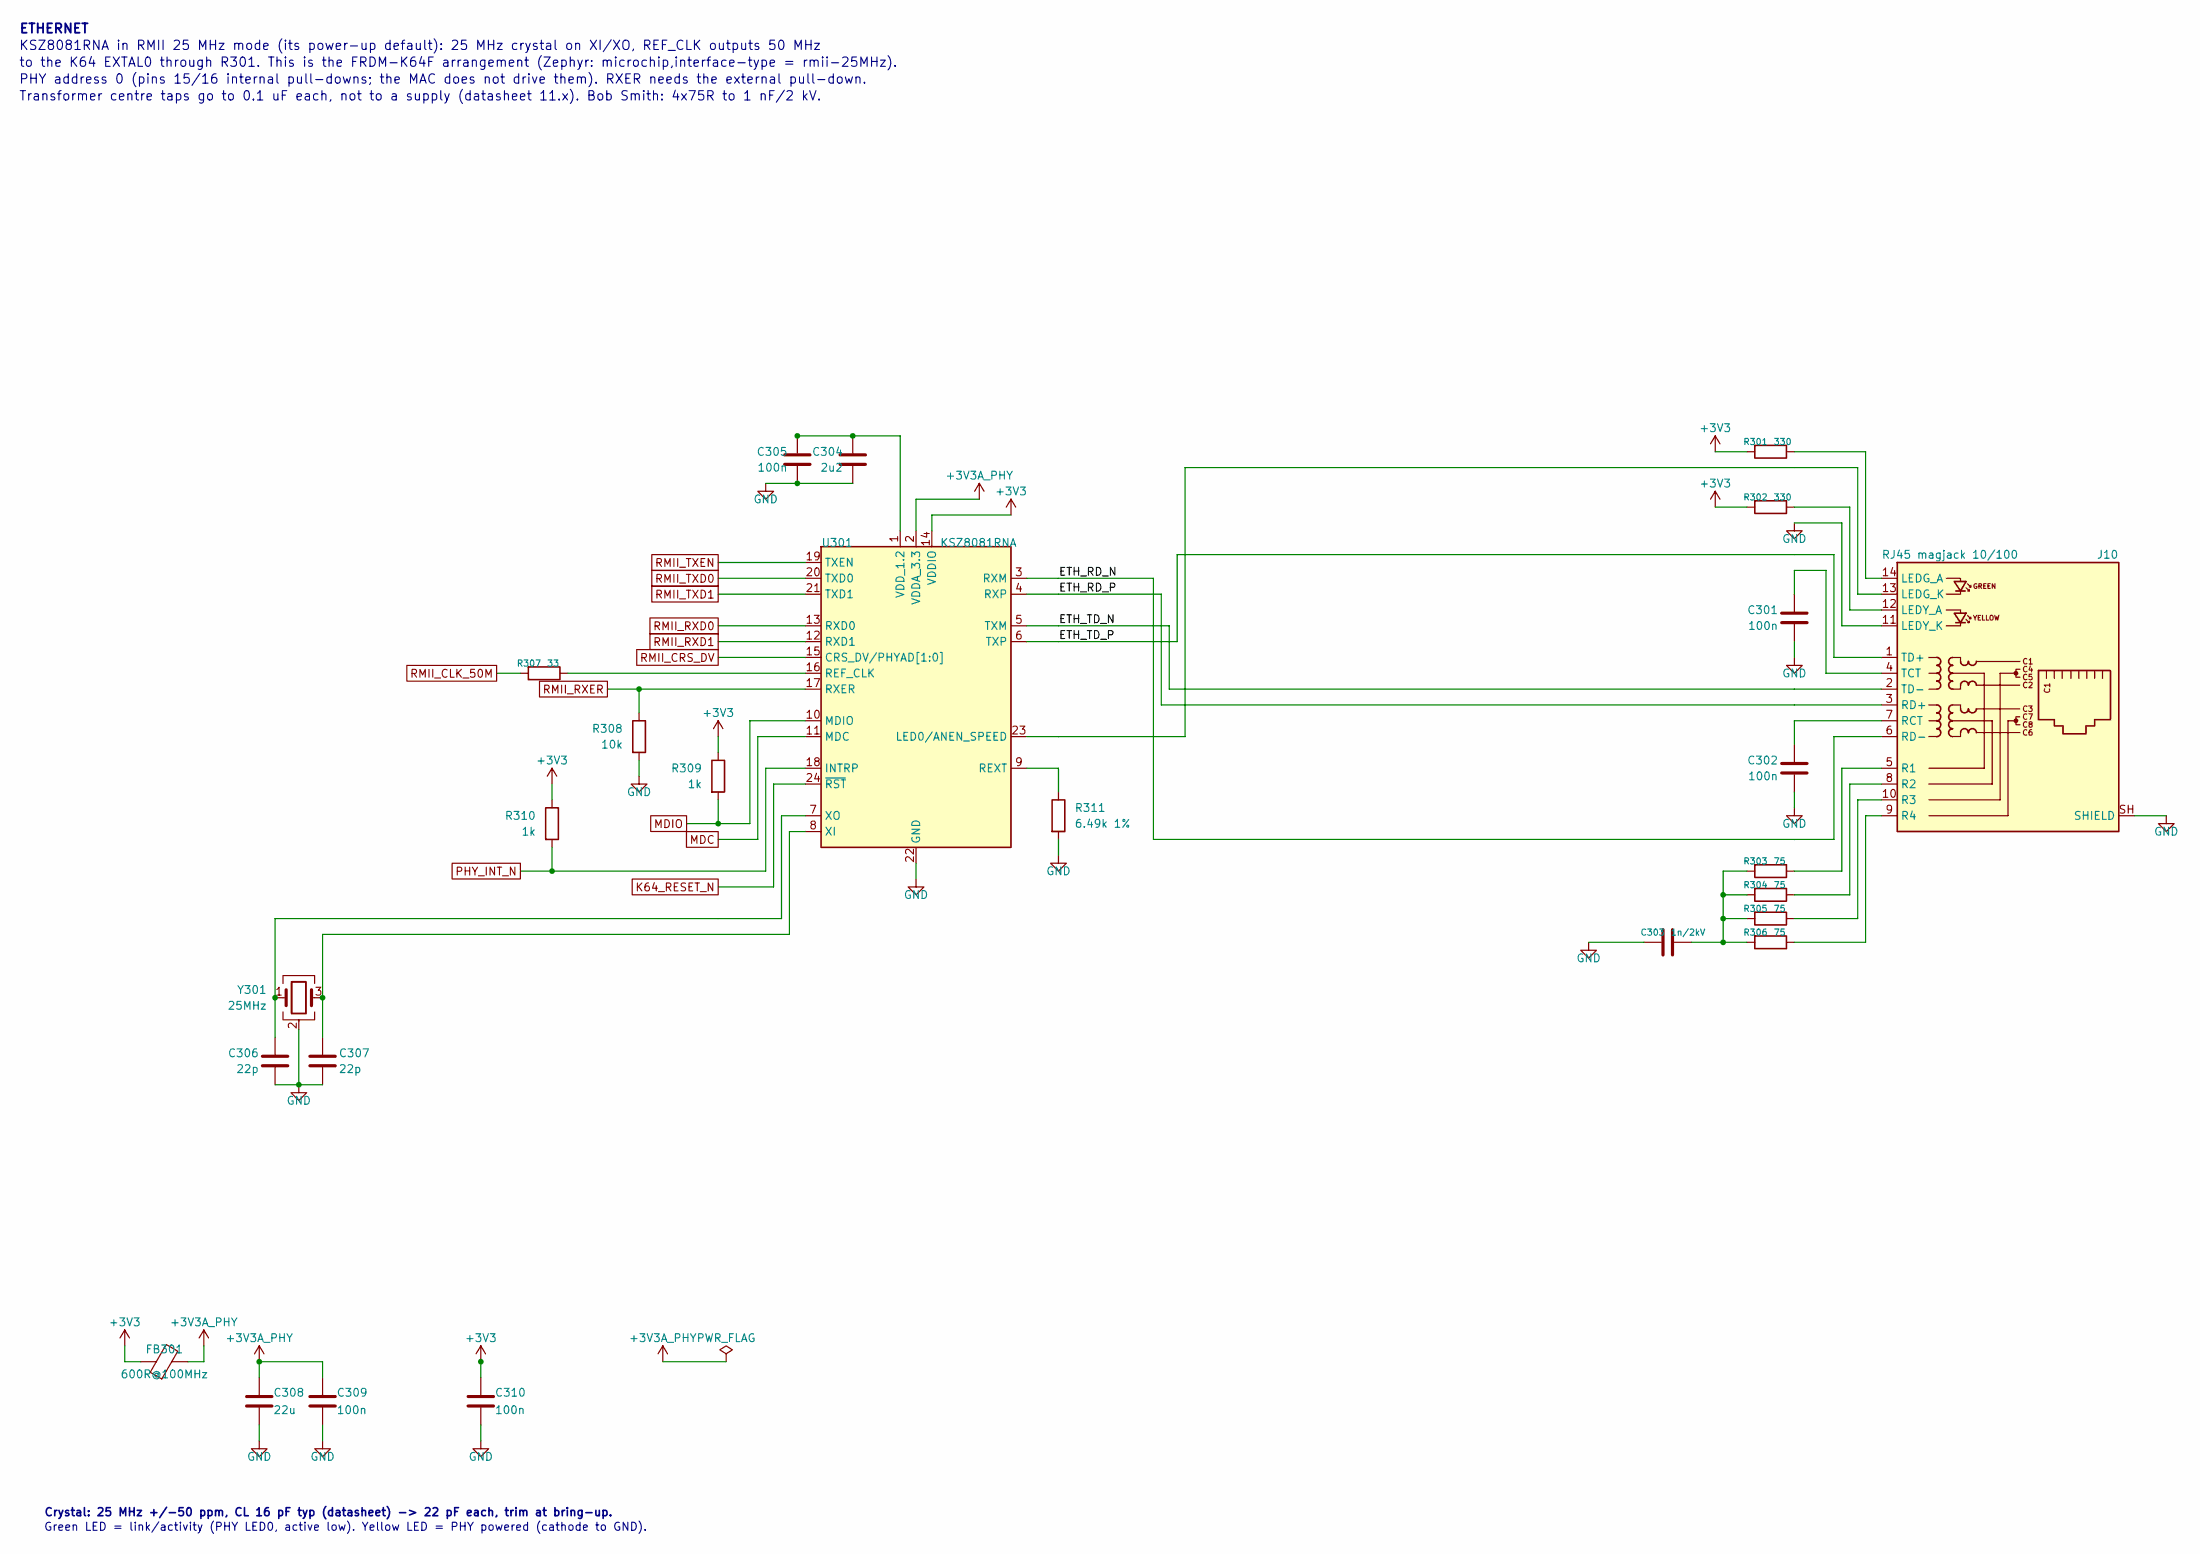
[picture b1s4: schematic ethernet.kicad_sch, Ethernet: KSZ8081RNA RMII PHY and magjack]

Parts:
C301, C302, C305, C309, C310: 100n; C_0603_1608Metric
C303: 1n/2kV; C_1206_3216Metric
C304: 2u2; C_0603_1608Metric
C306, C307: 22p; C_0603_1608Metric
C308: 22u; C_0805_2012Metric
FB301: 600R@100MHz; L_0603_1608Metric
J10: RJ45 magjack 10/100; RJ45_Kycon_G7LX-A88S7-BP-xx_Horizontal
R301, R302: 330; R_0603_1608Metric
R303, R304, R305, R306: 75; R_0603_1608Metric
R307: 33; R_0603_1608Metric
R308: 10k; R_0603_1608Metric
R309, R310: 1k; R_0603_1608Metric
R311: 6.49k 1%; R_0603_1608Metric
U301: KSZ8081RNA; QFN-24-1EP_4x4mm_P0.5mm_EP2.6x2.6mm
Y301: 25MHz; Crystal_SMD_3225-4Pin_3.2x2.5mm

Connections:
+3V3A_PHY: C308.1, C309.1, FB301.2, U301.2 (VDDA_3.3)
/Ethernet/ETH_RD_N: J10.6 (RD-), U301.3 (RXM)
/Ethernet/ETH_RD_P: J10.3 (RD+), U301.4 (RXP)
/Ethernet/ETH_TD_N: J10.2 (TD-), U301.5 (TXM)
/Ethernet/ETH_TD_P: J10.1 (TD+), U301.6 (TXP)
K64_RESET_N: U301.24 (~RST); also elsewhere on the board
MDC: U301.11 (MDC); also elsewhere on the board
MDIO: R309.2, U301.10 (MDIO); also elsewhere on the board
unnamed: C303.1, R303.2, R304.2, R305.2, R306.2
unnamed: J10.14 (LEDG_A), R301.1
unnamed: J10.13 (LEDG_K), U301.23 (LED0/ANEN_SPEED)
unnamed: J10.12 (LEDY_A), R302.1
unnamed: J10.5 (R1), R303.1
unnamed: J10.8 (R2), R304.1
unnamed: J10.10 (R3), R305.1
unnamed: J10.9 (R4), R306.1
unnamed: C302.1, J10.7 (RCT)
unnamed: C301.1, J10.4 (TCT)
unnamed: R307.1, U301.16 (REF_CLK)
unnamed: R311.1, U301.9 (REXT)
unnamed: C304.1, C305.1, U301.1 (VDD_1.2)
unnamed: C307.1, U301.8 (XI), Y301.3
unnamed: C306.1, U301.7 (XO), Y301.1
PHY_INT_N: R310.2, U301.18 (INTRP); also elsewhere on the board
RMII_CLK_50M: R307.2; also elsewhere on the board
RMII_CRS_DV: U301.15 (CRS_DV/PHYAD[1:0]); also elsewhere on the board
RMII_RXD0: U301.13 (RXD0); also elsewhere on the board
RMII_RXD1: U301.12 (RXD1); also elsewhere on the board
RMII_RXER: R308.1, U301.17 (RXER); also elsewhere on the board
RMII_TXD0: U301.20 (TXD0); also elsewhere on the board
RMII_TXD1: U301.21 (TXD1); also elsewhere on the board
RMII_TXEN: U301.19 (TXEN); also elsewhere on the board

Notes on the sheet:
ETHERNET
KSZ8081RNA in RMII 25 MHz mode (its power-up default): 25 MHz crystal on XI/XO, REF_CLK outputs 50 MHz
to the K64 EXTAL0 through R301. This is the FRDM-K64F arrangement (Zephyr: microchip,interface-type = rmii-25MHz).
PHY address 0 (pins 15/16 internal pull-downs; the MAC does not drive them). RXER needs the external pull-down.
Transformer centre taps go to 0.1 uF each, not to a supply (datasheet 11.x). Bob Smith: 4x75R to 1 nF/2 kV.
Crystal: 25 MHz +/-50 ppm, CL 16 pF typ (datasheet) -> 22 pF each, trim at bring-up.
Green LED = link/activity (PHY LED0, active low). Yellow LED = PHY powered (cathode to GND).
